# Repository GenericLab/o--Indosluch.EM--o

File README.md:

# o--Indosluch.EM--o
New pisibi and circuit for EM-sniffer, inspired by LOM's Elektrosluch (Error Static Zapper too), SOMA Ether, 1010 Detektor and Franzis' Bat-Detector and many others...

Goal: Make an affordable new and kinda modified / improved version of an EM sniffer in Yoygakarta, Indonesia. Use mainly parts that can be sourced locally on the common online shops or local stores.

Ideas:
* runs on 3V, LiPo, USB charging and / or powerbank
* single input / mono (mbe switched plug, to insert self-made antennas/coils)
* internal small speaker
* Volume knob
* Frequency shifting / demoluation of higher bandwidths to the audio range (with a knob to select bands)
* output mini-jack, 3.5mm
* beautifully crafted local teakwood casing
* ...

# Collaborators
* dusjagr
* Fiky
* Ucok

## Counselors
* Uwe, the Opa Master
* Ralf, another Opa Master

# Case study and mock-ups

# Reworking the Bat-Detector

Kicad version of the Fledermaus Detektor (bat-detector): https://www.elektronik-labor.de/Lernpakete/Fledermaus.html

# Inspriational Sources

## LOM's Elektrosluch (open Source)

Based on a single chip dual channel bi-polar Audio Operational Amplifier, opa1612, can be replaced by cheaper more noisier TL074  (suchas the Error Zapper). Runs on 9V. 

https://github.com/LOM-instruments/Elektrosluch-3-plus

## ERROR Zapper

Seems to be a clone, cheaper version of the Elektrosluch. No credits given :-(
Runs on 9V.

https://www.errorinstruments.com/a-60734445/new-synthe-noise-instruments-for-sale/error-zapper/#description

## SOMA Ether (everything is waves)

Based on a fist stage transistor amplification, and some kinda extra antenna on the board for higher frequency bands and a potentiomter for atenuation. Second stage with SSM2211 audio amplifier. Runs on 3V.

https://somasynths.com/ether/

## 1010 Detektor by Martin Howse (open Source)

Based on AD8313 HF-detektor (kinda expensive) and fist stage amplification with LM358, second LM386. Runs on 4.5V.

http://www.1010.co.uk/org/detektor.html

## Elektronik-Labor |  Bat-Detector (open Source) in german

Based on a first stage single transistor amplification, and a radio AM/FM chip CD2003 for high-frequency demodulation, frequency is adjusted with 555 timer. Final amplification stage with LM386. Original design runs on 9V, but lower voltage should work.

https://www.elektronik-labor.de/Lernpakete/Fledermaus.html

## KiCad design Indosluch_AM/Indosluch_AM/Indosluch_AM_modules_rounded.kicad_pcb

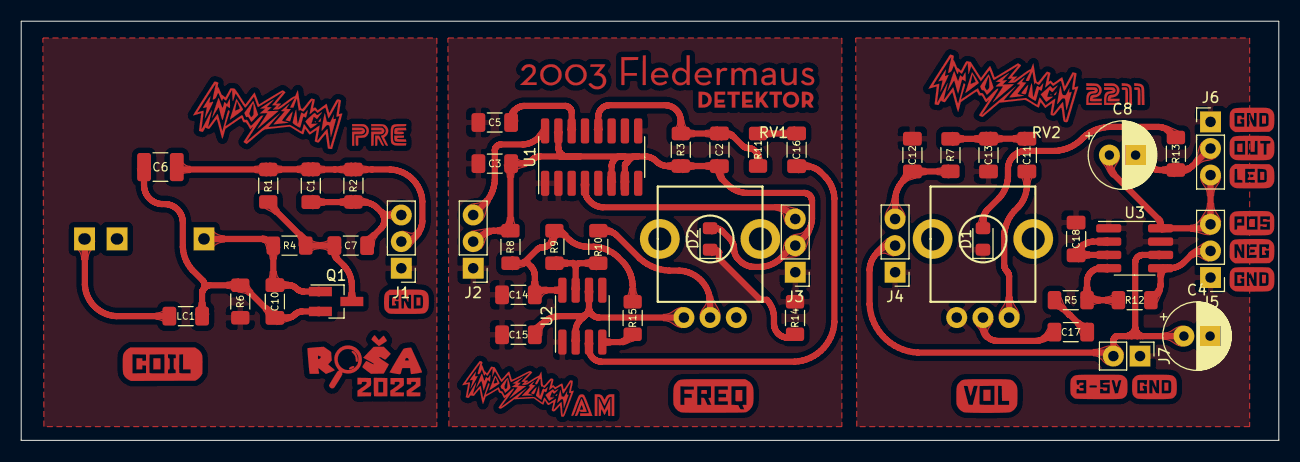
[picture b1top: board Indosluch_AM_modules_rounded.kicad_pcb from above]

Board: 2 copper layers, 120.0 x 40.0 mm, 50 parts (0 on the bottom side), 28 nets.

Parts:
C1, C2, C10, C15: 1nF; C_1206_dusjagr
C3, C5, C11, C12, C14, C16, C18: 100nF; C_1206_dusjagr
C4: 100uF; Capacitor_Radial_D6.3mm_P2.50mm
C6: 10uF; C_1210_dusjagr
C7: 3.3nF; C_1206_dusjagr
C8: 470uF; Capacitor_Radial_D6.3mm_P2.50mm
C13: 10nF; C_1206_dusjagr
C17: 470nF; C_1206_dusjagr
D1, D2: LED; LED_0805_2012Metric_Pad1.15x1.40mm_HandSolder
J1, J2, J3, J4, J5, J6: Con1x03; PinHeader_1x03_HandSolder
J7: Conn_01x02_Female; PinHeader_1x02_P2.54mm_HandSolder
L1: L 10-22mH; PJ301M-12_dusjagr_handSolder
LC1: C; C_1206_dusjagr
LOGO1: Logo; Indosluch_logos
Q1: BC849; SOT-23_Handsoldering
R1, R2, R6, R7: 1K; R_1206_dusjagr
R3, R8: 220; R_1206_dusjagr
R4: 470K; R_1206_dusjagr
R5, R12, R14: 10K; R_1206_dusjagr
R9, R11: 2K2; R_1206_dusjagr
R10: 3K3; R_1206_dusjagr
R13: 330; R_1206_dusjagr
R15: 0; R_1206_dusjagr
RV1: 22k lin; RD901F-ALPHA-HandSolder
RV2: 22k log; RD901F-ALPHA-HandSolder
U1: TA2003; SOP-16_HandSolder
U2: LM555xM; SOIC-8_HandSolder
U3: SSM2211S; SOIC-8_HandSolder

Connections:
AM-Filter-OUT: C17.2, RV2.2
AM-Mix-OUT: C12.1, J3.3, J4.3, R7.2, U1.4
GND: C3.1, C4.2, C5.2, C12.2, C13.2, C14.1, C15.1, C18.1, D1.1, J1.1, J2.1, J3.1, J4.1, J5.1, J6.1, J7.1, R6.2, R14.1, RV2.3, U1.1, U1.2, U1.9, U2.1, U3.1, U3.7
unnamed: C5.1, U1.14
unnamed: C7.2, Q1.3, R1.2, R4.1
unnamed: C8.2, J6.2, R13.2
unnamed: C11.1, RV2.1
unnamed: C11.2, C13.1, R7.1
unnamed: C14.2, R8.1, R9.2, R15.1, U2.8
unnamed: C15.2, RV1.3, U2.2, U2.6
unnamed: C16.1, R11.1
unnamed: C16.2, U2.3
unnamed: C17.1, R5.2
unnamed: C18.2, U3.2, U3.3
unnamed: D1.2, R13.1
unnamed: D2.1, R14.2
unnamed: L1.2, LC1.1
unnamed: R10.1, RV1.2
unnamed: R9.1, R10.2, U2.7
unnamed: R5.1, R12.2, U3.4
unnamed: R15.2, U2.4
OSC-IN: C2.1, R3.2, R11.2, U1.12
S-Neg: C6.2, C10.2, LC1.2, Q1.2, R6.1
S-Pos: C10.1, L1.1, Q1.1, R4.2
Speaker+Output: C8.1, J5.3, J6.3, U3.8
Speaker-Output: J5.2, R12.1, U3.5
TransistorOUT: C1.2, C7.1, J1.3, J2.3, R2.2, U1.16
VCC: C1.1, C2.2, C3.2, C4.1, C6.1, D2.2, J1.2, J2.2, J3.2, J4.2, J7.2, R1.1, R2.1, R3.1, R8.2, U1.6, U1.7, U1.15, U3.6

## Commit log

2022-10-14 new readme and link to inspirational sources
2022-10-14 adding sources
2022-10-14 more on readme
2022-10-19 kicad version of bat-detector
2022-10-19 editing readme
2022-10-26 new DIY version
2022-11-06 new DIY versions
2026-04-18 adding ralfs bat detector
